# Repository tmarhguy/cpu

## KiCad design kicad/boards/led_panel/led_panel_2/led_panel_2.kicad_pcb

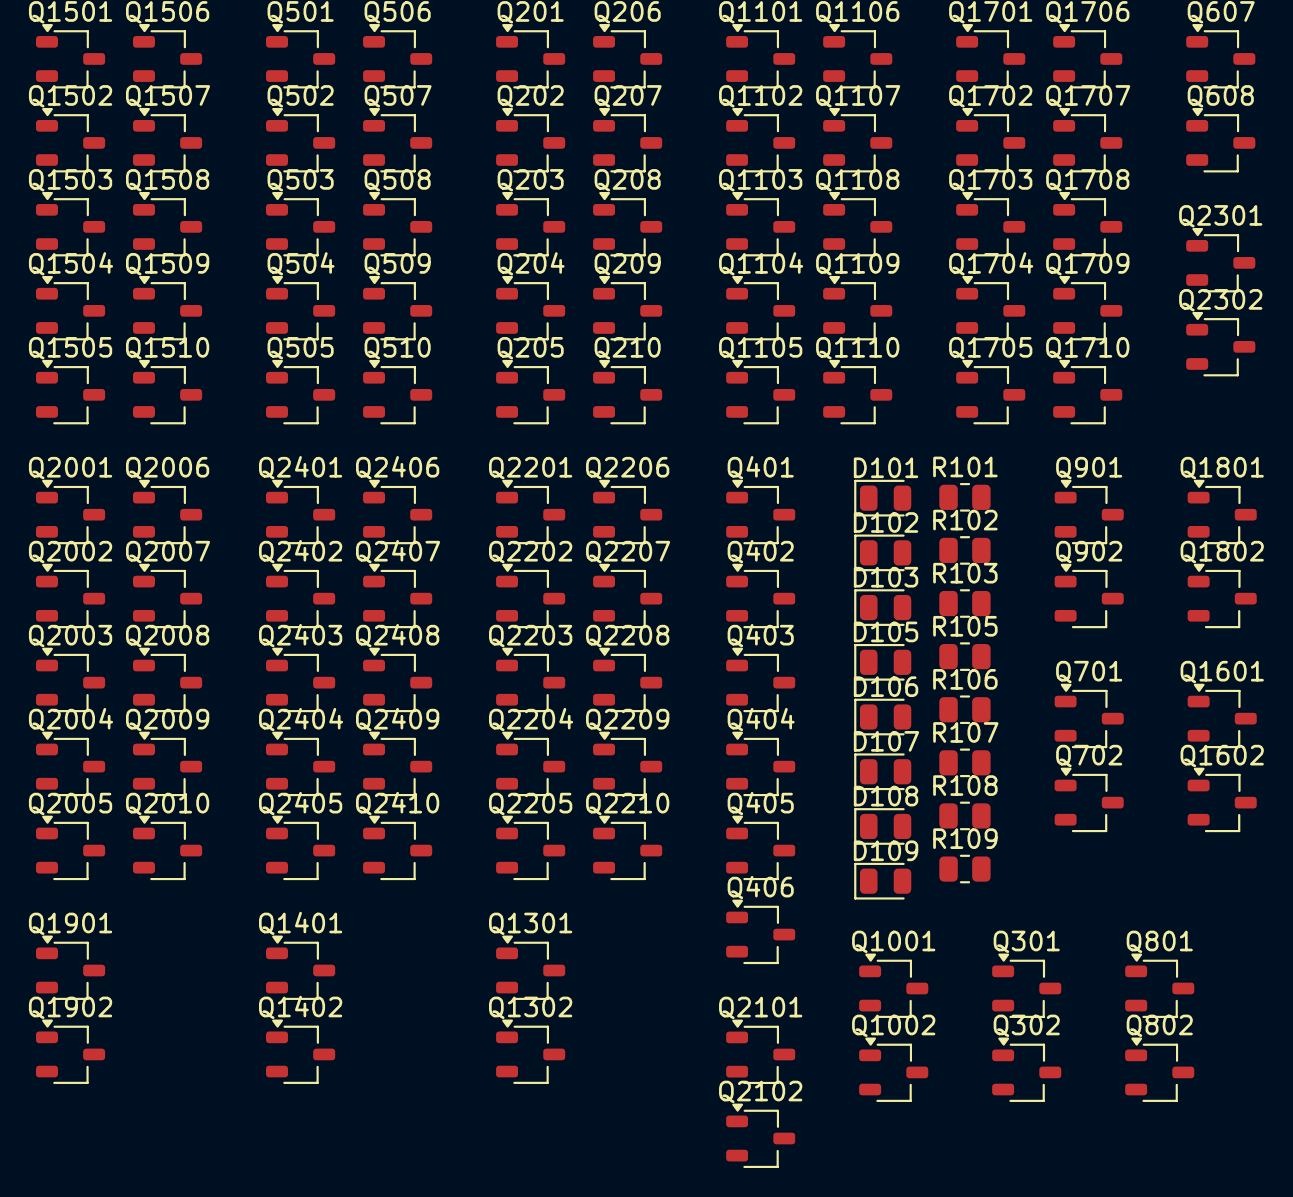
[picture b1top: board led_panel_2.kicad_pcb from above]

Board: 2 copper layers, 128 parts (0 on the bottom side), 71 nets, no tracks yet.

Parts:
D101: LED9; LED_0805_2012Metric
D102: LED8; LED_0805_2012Metric
D103: LED10; LED_0805_2012Metric
D105: LED11; LED_0805_2012Metric
D106: LED12; LED_0805_2012Metric
D107: LED13; LED_0805_2012Metric
D108: LED14; LED_0805_2012Metric
D109: LED15; LED_0805_2012Metric
Q201, Q202, Q203, Q208, Q209, Q301, Q401, Q404, Q405, Q501, Q502, Q503, Q508, Q509, Q607, Q701, Q801, Q901, Q1001, Q1101, Q1102, Q1103, Q1108, Q1109, Q1301, Q1401, Q1501, Q1502, Q1503, Q1508, Q1509, Q1601, Q1701, Q1702, Q1703, Q1708, Q1709, Q1801, Q1901, Q2001, Q2002, Q2003, Q2008, Q2009, Q2101, Q2201, Q2202, Q2203, Q2208, Q2209, Q2301, Q2401, Q2402, Q2403, Q2408, Q2409: PMOS; TSOT-23
Q204, Q205, Q206, Q207, Q210, Q302, Q402, Q403, Q406, Q504, Q505, Q506, Q507, Q510, Q608, Q702, Q802, Q902, Q1002, Q1104, Q1105, Q1106, Q1107, Q1110, Q1302, Q1402, Q1504, Q1505, Q1506, Q1507, Q1510, Q1602, Q1704, Q1705, Q1706, Q1707, Q1710, Q1802, Q1902, Q2004, Q2005, Q2006, Q2007, Q2010, Q2102, Q2204, Q2205, Q2206, Q2207, Q2210, Q2302, Q2404, Q2405, Q2406, Q2407, Q2410: NMOS; TSOT-23
R101, R102, R103, R105, R106, R107, R108, R109: 330; R_0805_2012Metric

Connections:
/2and2/A: Q401.2 (G), Q403.2 (G), Q1001.1 (D), Q1002.1 (D)
/4and2/B: Q502.2 (G), Q504.2 (G), Q607.1 (D), Q608.1 (D)
/4and2/C: Q301.1 (D), Q302.1 (D), Q506.2 (G), Q508.2 (G)
/4and2/D: Q501.2 (G), Q507.2 (G), Q701.1 (D), Q702.1 (D)
/4and2/Y: Q509.1 (D), Q510.1 (D), R102.1
/4and3/B: Q202.2 (G), Q204.2 (G), Q801.1 (D), Q802.1 (D)
/4and3/C: Q206.2 (G), Q208.2 (G), Q901.1 (D), Q902.1 (D)
/4and3/Y: Q209.1 (D), Q210.1 (D), R101.1
/4and4/B: Q1102.2 (G), Q1104.2 (G), Q1301.1 (D), Q1302.1 (D)
/4and4/D: Q1101.2 (G), Q1107.2 (G), Q1401.1 (D), Q1402.1 (D)
/4and4/Y: Q1109.1 (D), Q1110.1 (D), R103.1
/4and6/B: Q1502.2 (G), Q1504.2 (G), Q1601.1 (D), Q1602.1 (D)
/4and6/Y: Q1509.1 (D), Q1510.1 (D), R105.1
/4and7/C: Q1706.2 (G), Q1708.2 (G), Q1801.1 (D), Q1802.1 (D)
/4and7/D: Q1701.2 (G), Q1707.2 (G), Q1901.1 (D), Q1902.1 (D)
/4and7/Y: Q1709.1 (D), Q1710.1 (D), R106.1
/4and8/C: Q2006.2 (G), Q2008.2 (G), Q2101.1 (D), Q2102.1 (D)
/4and8/Y: Q2009.1 (D), Q2010.1 (D), R107.1
/4and9/D: Q2201.2 (G), Q2207.2 (G), Q2301.1 (D), Q2302.1 (D)
/4and9/Y: Q2209.1 (D), Q2210.1 (D), R108.1
/4and10/Y: Q2409.1 (D), Q2410.1 (D), R109.1
/CTRL0: Q201.2 (G), Q207.2 (G), Q701.2 (G), Q702.2 (G), Q1401.2 (G), Q1402.2 (G), Q1501.2 (G), Q1507.2 (G), Q1901.2 (G), Q1902.2 (G), Q2001.2 (G), Q2007.2 (G), Q2301.2 (G), Q2302.2 (G), Q2401.2 (G), Q2407.2 (G)
/CTRL1: Q301.2 (G), Q302.2 (G), Q901.2 (G), Q902.2 (G), Q1106.2 (G), Q1108.2 (G), Q1506.2 (G), Q1508.2 (G), Q1801.2 (G), Q1802.2 (G), Q2101.2 (G), Q2102.2 (G), Q2206.2 (G), Q2208.2 (G), Q2406.2 (G), Q2408.2 (G)
/CTRL2: Q607.2 (G), Q608.2 (G), Q801.2 (G), Q802.2 (G), Q1301.2 (G), Q1302.2 (G), Q1601.2 (G), Q1602.2 (G), Q1702.2 (G), Q1704.2 (G), Q2002.2 (G), Q2004.2 (G), Q2202.2 (G), Q2204.2 (G), Q2402.2 (G), Q2404.2 (G)
/CTRL3: Q402.2 (G), Q404.2 (G)
/CTRL4: Q1001.2 (G), Q1002.2 (G)
/sub_ctrl3: Q203.2 (G), Q205.2 (G), Q405.1 (D), Q406.1 (D), Q503.2 (G), Q505.2 (G), Q1103.2 (G), Q1105.2 (G), Q1503.2 (G), Q1505.2 (G), Q1703.2 (G), Q1705.2 (G), Q2003.2 (G), Q2005.2 (G), Q2203.2 (G), Q2205.2 (G), Q2403.2 (G), Q2405.2 (G)
GND: D101.1 (K), D102.1 (K), D103.1 (K), D105.1 (K), D106.1 (K), D107.1 (K), D108.1 (K), D109.1 (K), Q207.3 (S), Q210.3 (S), Q302.3 (S), Q403.3 (S), Q406.3 (S), Q507.3 (S), Q510.3 (S), Q608.3 (S), Q702.3 (S), Q802.3 (S), Q902.3 (S), Q1002.3 (S), Q1107.3 (S), Q1110.3 (S), Q1302.3 (S), Q1402.3 (S), Q1507.3 (S), Q1510.3 (S), Q1602.3 (S), Q1707.3 (S), Q1710.3 (S), Q1802.3 (S), Q1902.3 (S), Q2007.3 (S), Q2010.3 (S), Q2102.3 (S), Q2207.3 (S), Q2210.3 (S), Q2302.3 (S), Q2407.3 (S), Q2410.3 (S)
unnamed: D101.2 (A), R101.2
unnamed: D102.2 (A), R102.2
unnamed: D103.2 (A), R103.2
unnamed: D105.2 (A), R105.2
unnamed: D106.2 (A), R106.2
unnamed: D107.2 (A), R107.2
unnamed: D108.2 (A), R108.2
unnamed: D109.2 (A), R109.2
unnamed: Q201.1 (D), Q202.1 (D), Q203.1 (D), Q204.1 (D), Q208.1 (D), Q209.2 (G), Q210.2 (G)
unnamed: Q204.3 (S), Q205.1 (D)
unnamed: Q205.3 (S), Q206.1 (D)
unnamed: Q206.3 (S), Q207.1 (D)
unnamed: Q401.1 (D), Q402.1 (D), Q404.1 (D), Q405.2 (G), Q406.2 (G)
unnamed: Q402.3 (S), Q403.1 (D)
unnamed: Q501.1 (D), Q502.1 (D), Q503.1 (D), Q504.1 (D), Q508.1 (D), Q509.2 (G), Q510.2 (G)
unnamed: Q504.3 (S), Q505.1 (D)
unnamed: Q505.3 (S), Q506.1 (D)
unnamed: Q506.3 (S), Q507.1 (D)
unnamed: Q1101.1 (D), Q1102.1 (D), Q1103.1 (D), Q1104.1 (D), Q1108.1 (D), Q1109.2 (G), Q1110.2 (G)
unnamed: Q1104.3 (S), Q1105.1 (D)
unnamed: Q1105.3 (S), Q1106.1 (D)
unnamed: Q1106.3 (S), Q1107.1 (D)
unnamed: Q1501.1 (D), Q1502.1 (D), Q1503.1 (D), Q1504.1 (D), Q1508.1 (D), Q1509.2 (G), Q1510.2 (G)
unnamed: Q1504.3 (S), Q1505.1 (D)
unnamed: Q1505.3 (S), Q1506.1 (D)
unnamed: Q1506.3 (S), Q1507.1 (D)
unnamed: Q1701.1 (D), Q1702.1 (D), Q1703.1 (D), Q1704.1 (D), Q1708.1 (D), Q1709.2 (G), Q1710.2 (G)
unnamed: Q1704.3 (S), Q1705.1 (D)
unnamed: Q1705.3 (S), Q1706.1 (D)
unnamed: Q1706.3 (S), Q1707.1 (D)
unnamed: Q2001.1 (D), Q2002.1 (D), Q2003.1 (D), Q2004.1 (D), Q2008.1 (D), Q2009.2 (G), Q2010.2 (G)
unnamed: Q2004.3 (S), Q2005.1 (D)
unnamed: Q2005.3 (S), Q2006.1 (D)
unnamed: Q2006.3 (S), Q2007.1 (D)
unnamed: Q2201.1 (D), Q2202.1 (D), Q2203.1 (D), Q2204.1 (D), Q2208.1 (D), Q2209.2 (G), Q2210.2 (G)
unnamed: Q2204.3 (S), Q2205.1 (D)
unnamed: Q2205.3 (S), Q2206.1 (D)
unnamed: Q2206.3 (S), Q2207.1 (D)
unnamed: Q2401.1 (D), Q2402.1 (D), Q2403.1 (D), Q2404.1 (D), Q2408.1 (D), Q2409.2 (G), Q2410.2 (G)
unnamed: Q2404.3 (S), Q2405.1 (D)
unnamed: Q2405.3 (S), Q2406.1 (D)
unnamed: Q2406.3 (S), Q2407.1 (D)
VCC: Q201.3 (S), Q202.3 (S), Q203.3 (S), Q208.3 (S), Q209.3 (S), Q301.3 (S), Q401.3 (S), Q404.3 (S), Q405.3 (S), Q501.3 (S), Q502.3 (S), Q503.3 (S), Q508.3 (S), Q509.3 (S), Q607.3 (S), Q701.3 (S), Q801.3 (S), Q901.3 (S), Q1001.3 (S), Q1101.3 (S), Q1102.3 (S), Q1103.3 (S), Q1108.3 (S), Q1109.3 (S), Q1301.3 (S), Q1401.3 (S), Q1501.3 (S), Q1502.3 (S), Q1503.3 (S), Q1508.3 (S), Q1509.3 (S), Q1601.3 (S), Q1701.3 (S), Q1702.3 (S), Q1703.3 (S), Q1708.3 (S), Q1709.3 (S), Q1801.3 (S), Q1901.3 (S), Q2001.3 (S), Q2002.3 (S), Q2003.3 (S), Q2008.3 (S), Q2009.3 (S), Q2101.3 (S), Q2201.3 (S), Q2202.3 (S), Q2203.3 (S), Q2208.3 (S), Q2209.3 (S), Q2301.3 (S), Q2401.3 (S), Q2402.3 (S), Q2403.3 (S), Q2408.3 (S), Q2409.3 (S)

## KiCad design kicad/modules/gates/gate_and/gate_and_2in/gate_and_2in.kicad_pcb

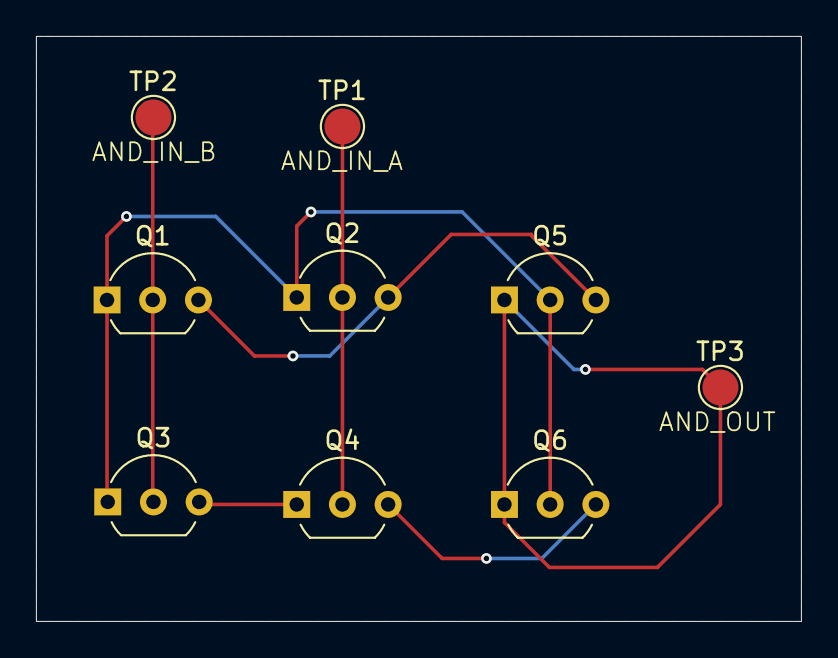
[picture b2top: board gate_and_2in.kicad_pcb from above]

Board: 2 copper layers, 42.5 x 32.5 mm, 9 parts (0 on the bottom side), 7 nets.

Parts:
Q1, Q2, Q5: PMOS; TO-92_Inline_Wide
Q3, Q4, Q6: NMOS; TO-92_Inline_Wide
TP1: AND_IN_A; TestPoint_Pad_D2.0mm
TP2: AND_IN_B; TestPoint_Pad_D2.0mm
TP3: AND_OUT; TestPoint_Pad_D2.0mm

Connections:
/AND_IN_A: Q2.2 (G), Q4.2 (G), TP1.1
/AND_IN_B: Q1.2 (G), Q3.2 (G), TP2.1
/AND_OUT: Q5.1 (D), Q6.1 (D), TP3.1
GND: Q4.3 (S), Q6.3 (S)
unnamed: Q1.1 (D), Q2.1 (D), Q3.1 (D), Q5.2 (G), Q6.2 (G)
unnamed: Q3.3 (S), Q4.1 (D)
VCC: Q1.3 (S), Q2.3 (S), Q5.3 (S)

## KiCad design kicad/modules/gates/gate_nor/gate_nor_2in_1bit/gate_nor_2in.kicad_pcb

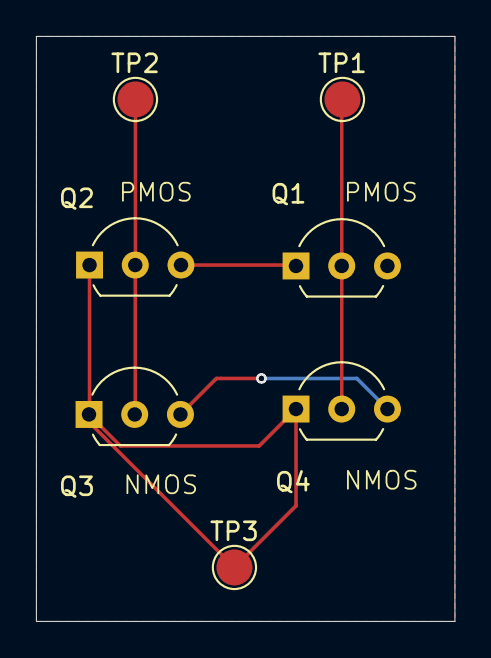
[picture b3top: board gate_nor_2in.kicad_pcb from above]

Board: 2 copper layers, 23.2 x 32.5 mm, 7 parts (0 on the bottom side), 5 nets.

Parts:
Q1, Q2: PMOS; TO-92L_Inline_Wide
Q3, Q4: NMOS; TO-92L_Inline_Wide
TP1, TP2: NOR_IN_B; TestPoint_Pad_D2.0mm
TP3: NOT_OUT; TestPoint_Pad_D2.0mm

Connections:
/NOR_IN_A: Q1.2 (G), Q4.2 (G), TP1.1
/NOR_IN_B: Q2.2 (G), Q3.2 (G), TP2.1
/NOR_OUT: Q2.1 (D), Q3.1 (D), Q4.1 (D), TP3.1
GND: Q3.3 (S), Q4.3 (S)
unnamed: Q1.1 (D), Q2.3 (S)

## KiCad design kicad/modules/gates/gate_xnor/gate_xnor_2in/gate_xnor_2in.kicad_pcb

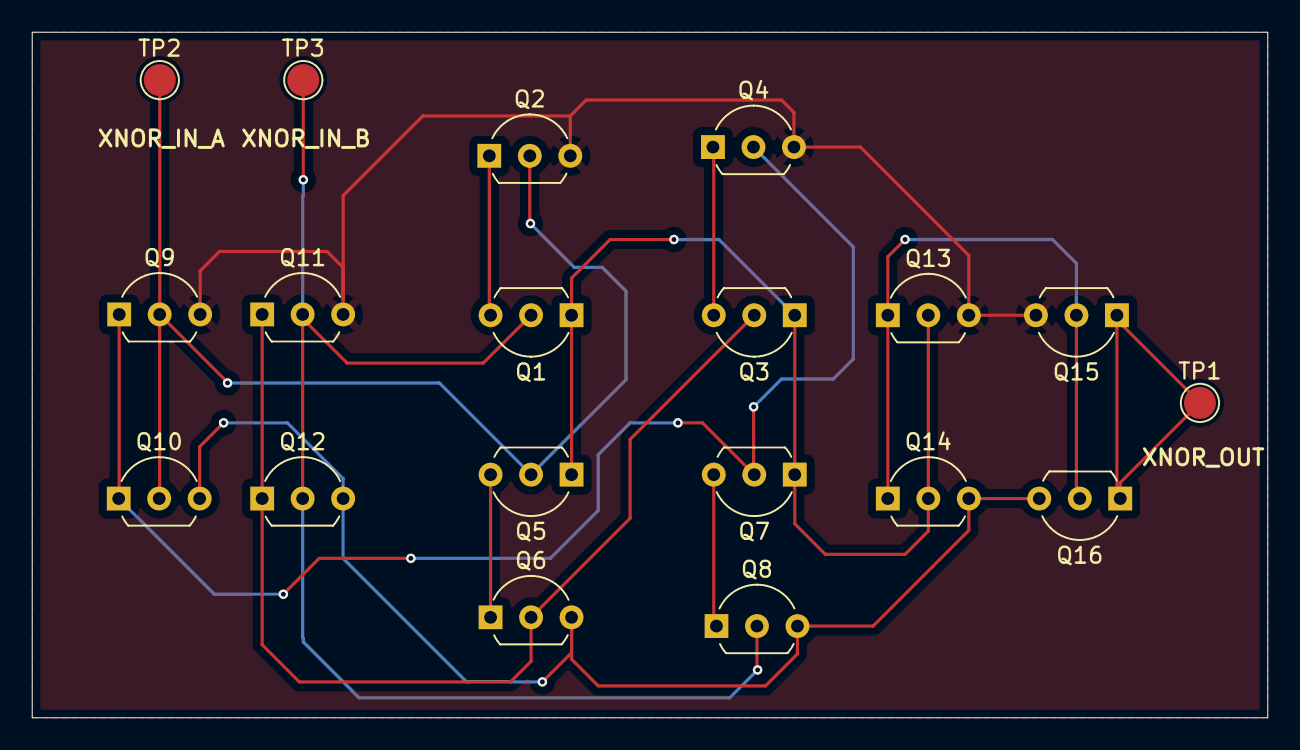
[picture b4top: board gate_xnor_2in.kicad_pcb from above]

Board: 2 copper layers, 77.5 x 43.0 mm, 19 parts (0 on the bottom side), 13 nets.

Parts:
Q1, Q2, Q3, Q4, Q9, Q11, Q13, Q15: PMOS; TO-92L_Inline_Wide
Q5, Q6, Q7, Q8, Q10, Q12, Q14, Q16: NMOS; TO-92L_Inline_Wide
TP1: XNOR_OUT; TestPoint_Pad_D2.0mm
TP2: XNOR_IN_A; TestPoint_Pad_D2.0mm
TP3: XNOR_IN_B; TestPoint_Pad_D2.0mm

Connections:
/XNOR_IN_A: Q2.2 (G), Q5.2 (G), Q9.2 (G), Q10.2 (G), TP2.1
/XNOR_IN_B: Q1.2 (G), Q8.2 (G), Q11.2 (G), Q12.2 (G), TP3.1
/XNOR_OUT: Q15.1 (D), Q16.1 (D), TP1.1
GND: Q6.3 (S), Q8.3 (S), Q10.3 (S), Q12.3 (S), Q14.3 (S), Q16.3 (S)
unnamed: Q1.1 (D), Q3.1 (D), Q5.1 (D), Q7.1 (D), Q13.2 (G), Q14.2 (G)
unnamed: Q1.3 (S), Q2.1 (D)
unnamed: Q3.3 (S), Q4.1 (D)
unnamed: Q5.3 (S), Q6.1 (D)
unnamed: Q7.3 (S), Q8.1 (D)
unnamed: Q4.2 (G), Q7.2 (G), Q9.1 (D), Q10.1 (D)
unnamed: Q3.2 (G), Q6.2 (G), Q11.1 (D), Q12.1 (D)
unnamed: Q13.1 (D), Q14.1 (D), Q15.2 (G), Q16.2 (G)
VCC: Q2.3 (S), Q4.3 (S), Q9.3 (S), Q11.3 (S), Q13.3 (S), Q15.3 (S)

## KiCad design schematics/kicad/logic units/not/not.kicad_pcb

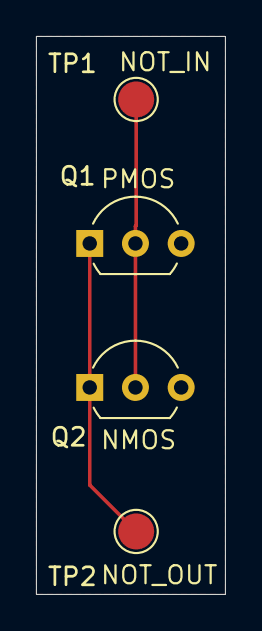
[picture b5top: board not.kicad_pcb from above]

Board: 2 copper layers, 10.5 x 31.0 mm, 4 parts (0 on the bottom side), 2 nets.

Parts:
Q1: PMOS; TO-92L_Inline_Wide
Q2: NMOS; TO-92L_Inline_Wide
TP1: NOT_IN; TestPoint_Pad_D2.0mm
TP2: NOT_OUT; TestPoint_Pad_D2.0mm

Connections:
/NOT_IN: Q1.2 (G), Q2.2 (G), TP1.1
/NOT_OUT: Q1.1 (D), Q2.1 (D), TP2.1
